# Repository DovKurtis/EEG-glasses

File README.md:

Long-Goal: Establish continuous, real-world, multimodal data (visual, auditory, physiological, neural) as the standard for meaningful insights in emotional and personality disorder BCI applications. The system emphasizes electrode stability and signal protection. 

# EEG-glasses

## PCB

EEG Glasses is an early-stage research project developing wearable EEG glasses to address the lack of high-quality, real-world, naturalistic, multimodal neural data. The system is designed exclusively for clean, reliable signal acquisition in unconstrained environments, emphasizing electrode stability, low-noise amplification, and signal protection. It is in active prototyping and experimentation and is not intended for wellness or consumer use.

The long-term goal is a sleek, unobtrusive sensing platform that makes neural data collection a normal, everyday tool for scalable real-world BCI and cognitive neuroscience research.

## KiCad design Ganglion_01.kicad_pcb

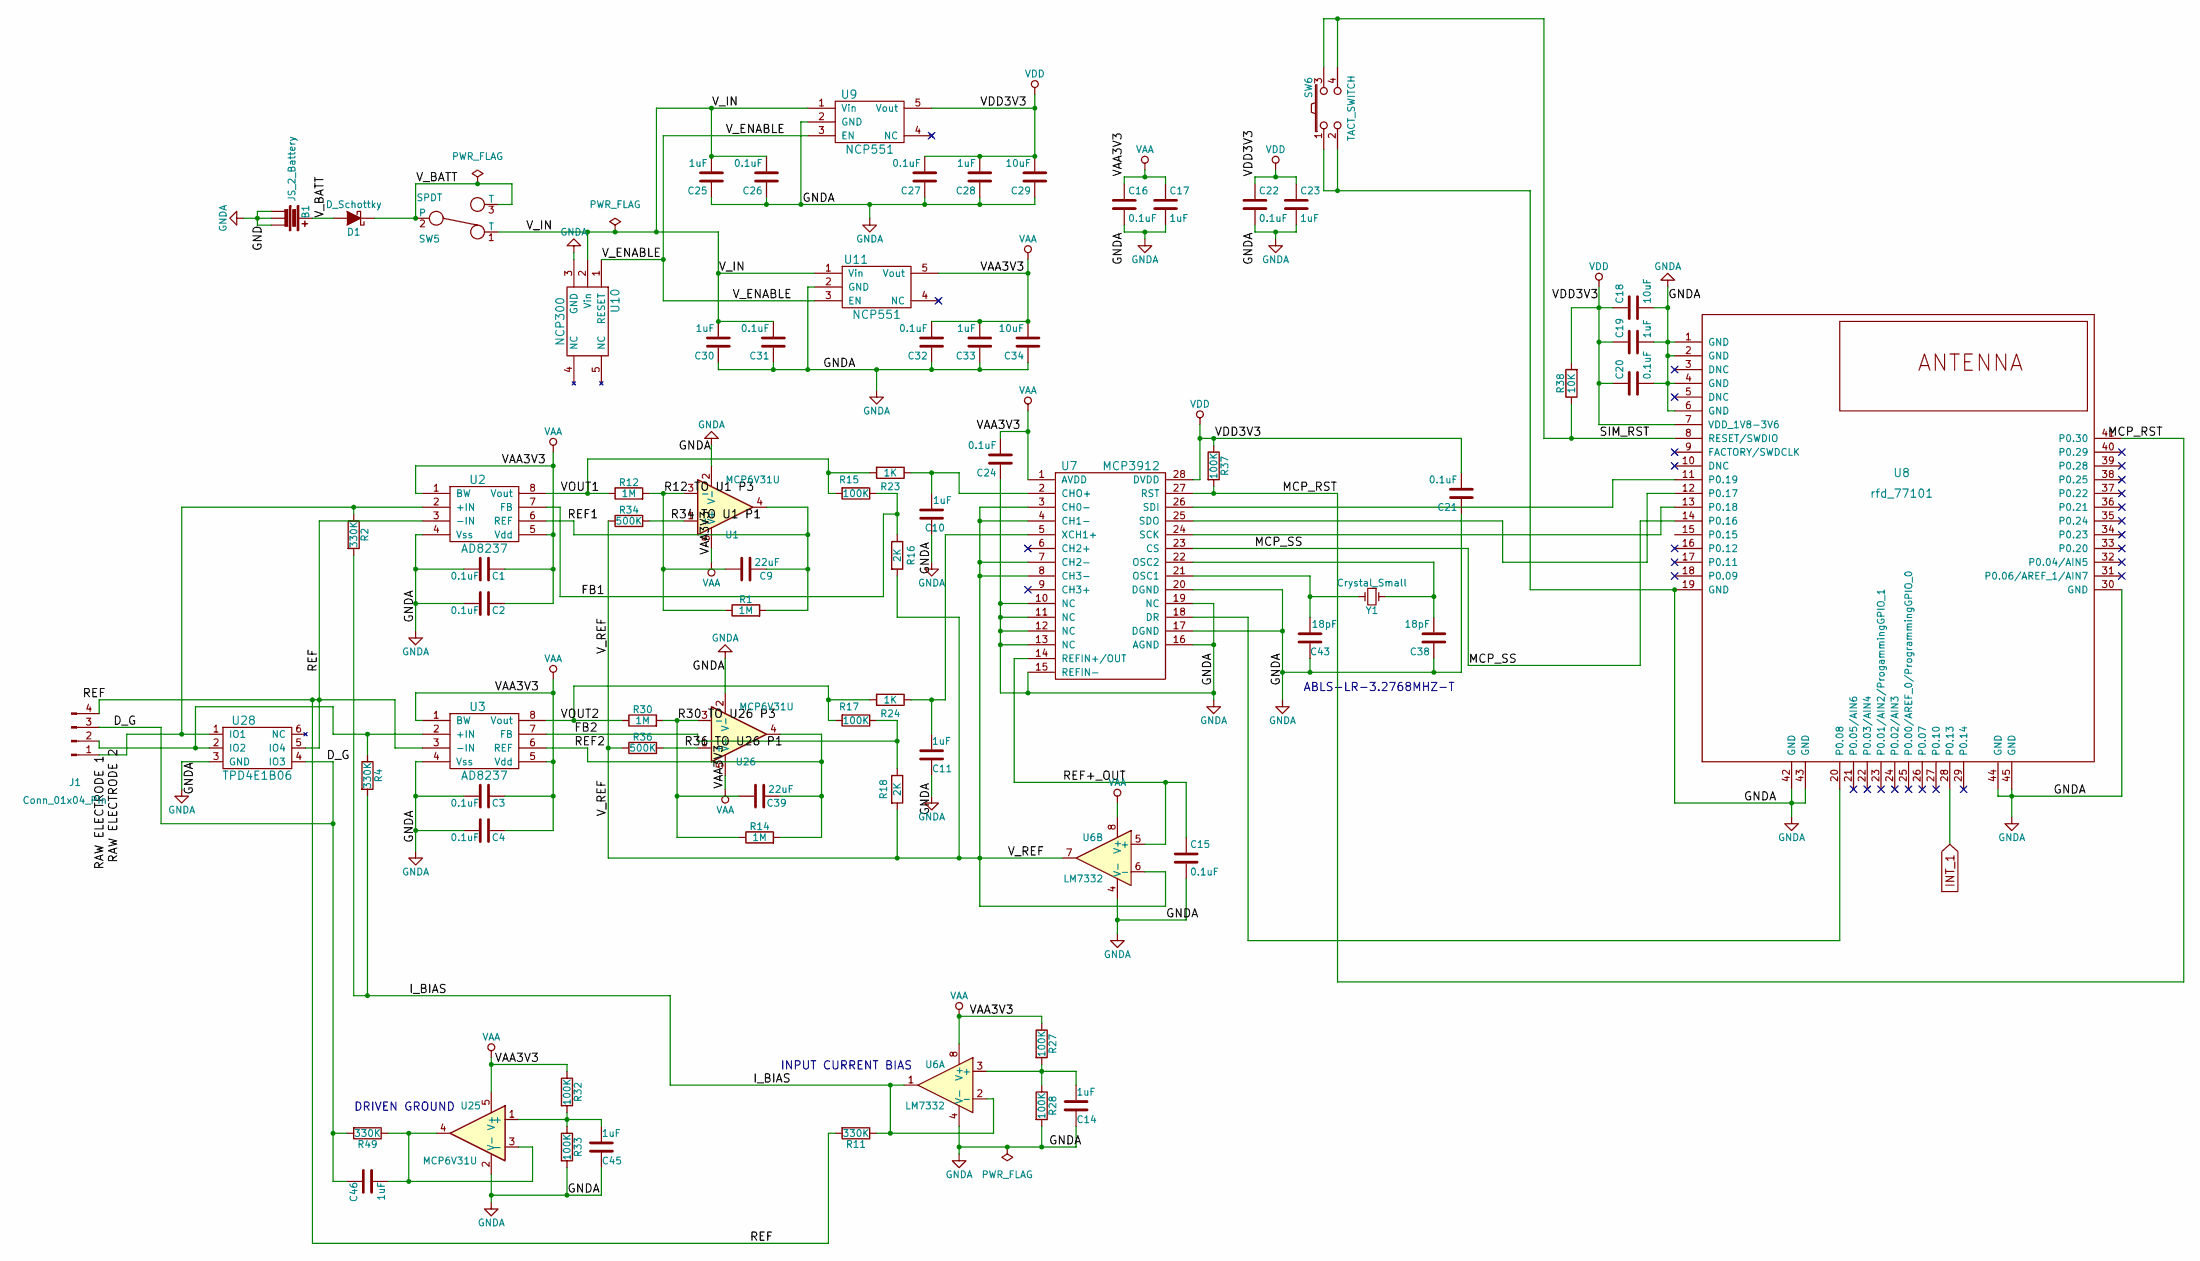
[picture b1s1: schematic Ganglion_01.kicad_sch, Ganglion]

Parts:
B1: JS_2_Battery; JS_2_BATTERY; PART NUMBER S2B-PH-SM4-TB(LF)(SN)
C1, C2, C3, C4, C15, C16, C20, C21, C22, C24, C26, C27, C31, C32: 0.1uF; C_0603_1608Metric; PART NUMBER GRM188R71H104KA93D
C9, C39: 22uF; C_0603_1608Metric; PART NUMBER GRM188R60J226MEA0D
C10, C11, C14, C17, C19, C23, C25, C28, C30, C33, C45, C46: 1uF; C_0603_1608Metric; PART NUMBER GRM188R61E105KA12D
C18, C29, C34: 10uF; C_0603_1608Metric; PART NUMBER GRM188C80G106ME47D
C38, C43: 18pF; C_0603_1608Metric; PART NUMBER GRM1885C1H180JA01D
D1: D_Schottky; D_SCHOTTKY; PART NUMBER CDBU0130L
J1: Conn_01x04_Pin; PinHeader_1x04_P2.54mm_Vertical; PART NUMBER 929705-01-04-EU
R1, R12, R14, R30: 1M; R_0603_1608Metric; PART NUMBER ERJ-3EKF1004V
R2, R4, R11, R49: 330K; R_0603_1608Metric; PART NUMBER ERJ-3EKF3303V
R15, R17, R27, R28, R32, R33, R37: 100K; R_0603_1608Metric; PART NUMBER ERJ-3EKF1003V
R16, R18: 2K; R_0603_1608Metric; PART NUMBER ERJ-3EKF2001V
R23, R24: 1K; R_0603_1608Metric; PART NUMBER ERJ-3EKF1001V
R34, R36: 500K; R_0603_1608Metric; PART NUMBER CR0603-FX-4993ELF
R38: 10K; R_0603_1608Metric; PART NUMBER ERJ-3EKF1002V
SW5: SPDT; SW_BATT; PART NUMBER SSSS810701
SW6: TACT_SWITCH; SW6_BUTTON; PART NUMBER PTS810 SJK 250 SMTR LFS
U1, U25, U26: MCP6V31U; PART NUMBER MCP6V31UT-E/LT
U2, U3: AD8237; PART NUMBER AD8237ARMZ-R7
U6: LM7332; PART NUMBER MCP6L02T-E/MS
U7: MCP3912; PART NUMBER MCP3912A1-E/SS
U8: rfd_77101; RFD77101; PART NUMBER RFD-77101
U9, U11: NCP551; PART NUMBER NCP551SN30T1G
U10: NCP300; PART NUMBER NCP300LSN30T1G
U28: TPD4E1B06; PART NUMBER TPD4E1B06DCKR
Y1: Crystal_Small; Crystal_HC49-SD_SMD; PART NUMBER ABLS-LR-3.2768MHZ-T

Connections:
/D_G: C46.2, J1.3, R49.2, U28.4 (IO3)
/FB1: R15.1, R16.1, U2.7 (FB)
/FB2: R17.1, R18.1, U3.7 (FB)
/I_BIAS: R2.2, R4.2, R11.1, U6.1, U6.2 (-)
/MCP_RST: R37.2, U7.27 (RST), U8.41 (P0.30)
/MCP_SS: U7.23 (CS), U8.14 (P0.16)
/R12 TO U1 P3: C9.1, R1.1, R12.2, U1.3 (-)
/R30 TO U26 P3: C39.1, R14.1, R30.2, U26.3 (-)
/R34 TO U1 P1: R34.2, U1.1 (+)
/R36 TO U26 P1: R36.2, U26.1 (+)
/RAW ELECTRODE 1: J1.1, R2.1, U2.2 (+IN), U28.1 (IO1)
/RAW ELECTRODE 2: J1.2, R4.1, U3.2 (+IN), U28.2 (IO2)
/REF: J1.4, R11.2, U2.3 (-IN), U3.3 (-IN), U28.5 (IO4)
/REF1: C9.2, R1.2, U1.4, U2.6 (REF)
/REF2: C39.2, R14.2, U3.6 (REF), U26.4
/REF+_OUT: C15.1, U6.5 (+), U7.14 (REFIN+/OUT)
/SIM_RST: R38.1, SW6.3, SW6.4, U8.8 (RESET/SWDIO)
/VOUT1: R12.1, R15.2, R23.2, U2.8 (Vout)
/VOUT2: R17.2, R24.2, R30.1, U3.8 (Vout)
/V_BATT: B1.1, D1.1 (K), D1.2 (A), SW5.2, SW5.3 (T)
/V_ENABLE: U9.3 (EN), U10.1 (RESET), U11.3 (EN)
/V_IN: C25.2, C26.2, C30.2, C31.2, SW5.1 (T), U9.1 (Vin), U10.2 (Vin), U11.1 (Vin)
/V_REF: R16.2, R18.2, R34.1, R36.1, U6.6 (-), U6.7, U7.3 (CH0-), U7.4 (CH1-), U7.7 (CH2-), U7.8 (CH3-)
GNDA: B1.2, B1.3, B1.4, C1.2, C2.2, C3.2, C4.2, C10.1, C11.2, C14.2, C15.2, C16.2, C17.2, C18.2, C19.2, C20.2, C21.1, C22.2, C23.2, C24.1, C25.1, C26.1, C27.1, C28.1, C29.1, C30.1, C31.1, C32.1, C33.1, C34.1, C38.1, C43.1, C45.2, R28.2, R33.2, SW6.1, SW6.2, U1.2 (V-), U2.4 (Vss), U3.4 (Vss), U6.4 (V-), U7.10 (NC), U7.11 (NC), U7.12 (NC), U7.13 (NC), U7.15 (REFIN-), U7.16 (AGND), U7.17 (DGND), U7.19 (NC), U7.20 (DGND), U8.1 (GND), U8.2 (GND), U8.4 (GND), U8.6 (GND), U8.19 (GND), U8.30 (GND), U8.42 (GND), U8.43 (GND), U8.44 (GND), U8.45 (GND), U9.2 (GND), U10.3 (GND), U11.2 (GND), U25.2 (V-), U26.2 (V-), U28.3 (GND)
INT_1: U8.28 (P0.13)
unnamed: C14.1, R27.2, R28.1, U6.3 (+)
unnamed: C10.2, R23.1, U7.2 (CHO+)
unnamed: U7.18 (DR), U8.20 (P0.08)
unnamed: C43.2, U7.21 (OSC1), Y1.2
unnamed: C38.2, U7.22 (OSC2), Y1.1
unnamed: U7.24 (SCK), U8.13 (P0.18)
unnamed: U7.26 (SDI), U8.11 (P0.19)
unnamed: U7.25 (SDO), U8.12 (P0.17)
unnamed: C11.1, R24.1, U7.5 (XCH1+)
unnamed: C45.1, R32.2, R33.1, U25.1 (+)
unnamed: C46.1, R49.1, U25.3 (-), U25.4
VAA: C1.1, C2.1, C3.1, C4.1, C16.1, C17.1, C24.2, C32.2, C33.2, C34.2, R27.1, R32.1, U1.5 (V+), U2.1 (BW), U2.5 (Vdd), U3.1 (BW), U3.5 (Vdd), U6.8 (V+), U7.1 (AVDD), U11.5 (Vout), U25.5 (V+), U26.5 (V+)
VDD: C18.1, C19.1, C20.1, C21.2, C22.1, C23.1, C27.2, C28.2, C29.2, R37.1, R38.2, U7.28 (DVDD), U8.7 (VDD_1V8-3V6), U9.5 (Vout)

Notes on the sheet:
ABLS-LR-3.2768MHZ-T
INPUT CURRENT BIAS
DRIVEN GROUND

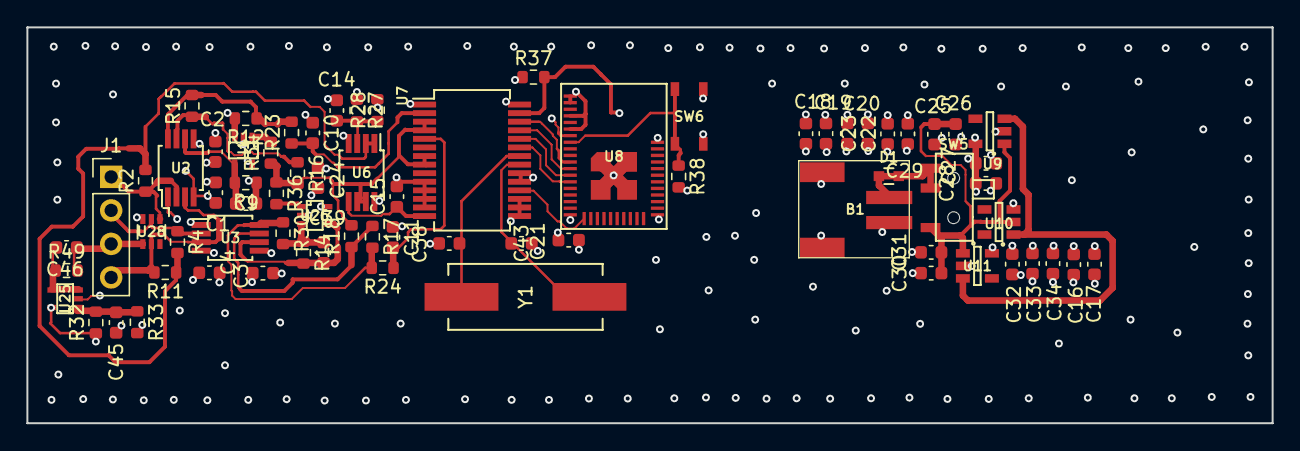
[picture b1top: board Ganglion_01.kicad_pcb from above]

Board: 4 copper layers, 94.4 x 30.0 mm, 73 parts (0 on the bottom side), 37 nets.

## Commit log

2026-02-07 Update and rename Ganglion_01.kicad_pcb to
2026-02-17 Update README with images and project details
    Added images and enhanced project description in README.
2026-02-17 Update README with PCB images
    Added images of the PCB components to the README.
2026-02-24 Add long-term goal for BCI applications
    Added a long-term goal statement for the project.
2026-02-24 Update long-term goal statement in README
    Removed mention of active prototyping and consumer use from the long-term goal statement.
